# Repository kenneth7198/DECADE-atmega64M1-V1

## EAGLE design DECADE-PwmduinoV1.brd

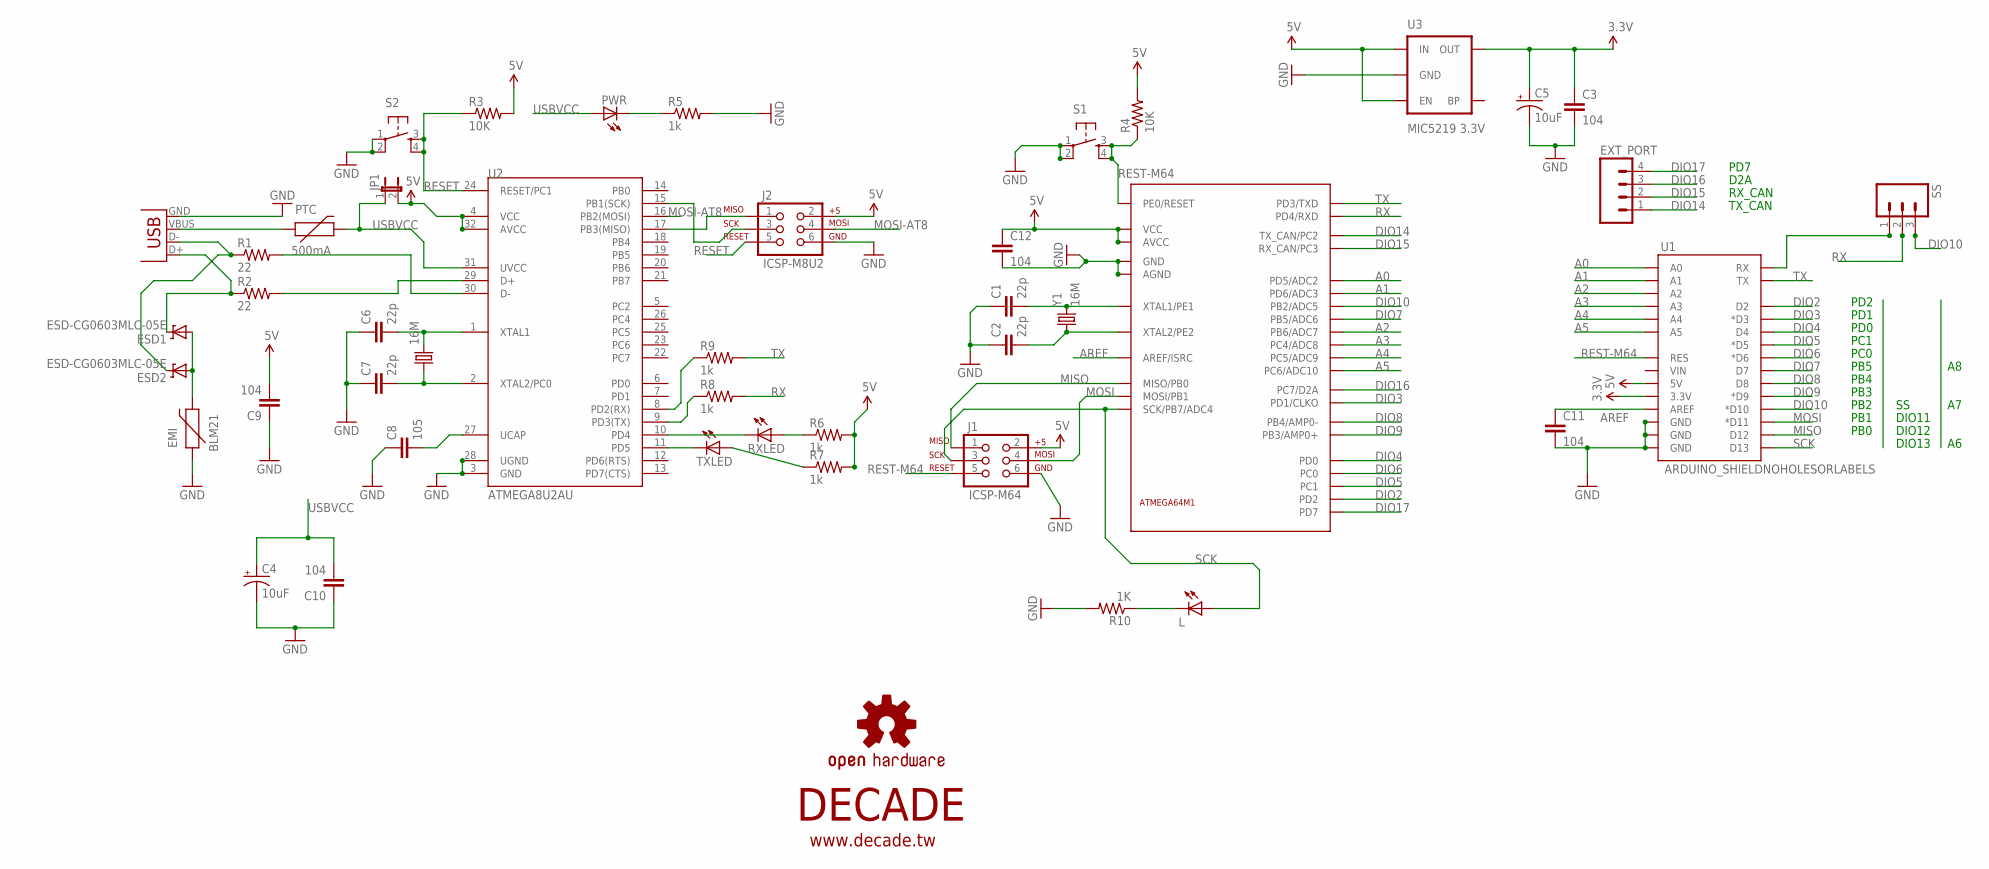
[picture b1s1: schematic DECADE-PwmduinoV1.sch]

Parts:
16M: CRYSTAL5X3; CRYSTAL-SMD-5X3
C1, C2, C6, C7: 22p; 0603-CAP
C3, C9, C10, C11, C12: 104; 0603-CAP
C4, C5: 10uF; EIA3216-KIT
C8: 105; 0603-CAP
EMI: BLM21; PTC-1206
ESD1, ESD2: ESD-CG0603MLC-05E; SOD-323
EXT_PORT: M04LOCK; 1X04_LOCK
J1: ICSP-M64; 2X3_LOCK
J2: ICSP-M8U2; 2X3_LOCK
JP1: JUMPER-2SMD-NO; SJ_2S-NO
L: LEDCHIP-LED0603; CHIP-LED0603
LOGO1: OSHW-LOGOL; OSHW-LOGO-L
PTC: 500mA; SPARKFUN_PTC-1206
PWR: LEDCHIP-LED0603; CHIP-LED0603
R1, R2: 22; SPARKFUN_0603-RES
R3, R4: 10K; SPARKFUN_0603-RES
R5, R6, R7, R8, R9: 1k; SPARKFUN_0603-RES
R10: 1K; SPARKFUN_0603-RES
RXLED: LEDCHIP-LED0603; CHIP-LED0603
S1: TAC_SWITCHPTH; TACTILE-PTH
S2: TAC_SWITCHSMD; TACTILE_SWITCH_SMD
SS: M03LOCK; 1X03_LOCK
TXLED: LEDCHIP-LED0603; CHIP-LED0603
U1: ARDUINO_SHIELDNOHOLESORLABELS; DUEMILANOVE_SHIELD_NOHOLES_NOLABELS
U2: ATMEGA8U2AU; TQFP32-08
U3: MIC5219 3.3V; SOT23-5
U$1: DECADE-ATMEGA64M1; DECADE-QFN-32
U$2: DECADE-LOGO-SMALL
X1: SPARKFUN_USBOLD; SPARKFUN_USB-MINIB-OLD
Y1: 16M; CRYSTAL-SMD-5X3

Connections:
3.3V: C3.1, C5.A (+), U1.3.3V, U3.5 (OUT)
5V: C9.2, C12.1, J1.2, J2.2, JP1.2, R3.2, R4.2, R6.2, R7.2, U1.5V, U2.4 (VCC), U2.32 (AVCC), U3.1 (IN), U3.3 (EN), U$1.4 (VCC), U$1.19 (AVCC)
A0: U1.A0, U$1.13 (PD5/ADC2)
A1: U1.A1, U$1.14 (PD6/ADC3)
A2: U1.A2, U$1.27 (PB6/ADC7)
A3: U1.A3, U$1.17 (PC4/ADC8)
A4: U1.A4, U$1.18 (PC5/ADC9)
A5: U1.A5, U$1.22 (PC6/ADC10)
AREF: C11.1, U1.AREF, U$1.21 (AREF/ISRC)
DIO2: U1.D2, U$1.1 (PD2)
DIO3: U1.D3 (*D3), U$1.32 (PD1/CLKO)
DIO4: U1.D4, U$1.29 (PD0)
DIO5: U1.D5 (*D5), U$1.3 (PC1)
DIO6: U1.D6 (*D6), U$1.30 (PC0)
DIO7: U1.D7, U$1.26 (PB5/ADC6)
DIO8: U1.D8, U$1.24 (PB4/AMP0-)
DIO9: U1.D9 (*D9), U$1.23 (PB3/AMP0+)
DIO10: SS.3, U1.D10 (*D10), U$1.16 (PB2/ADC5)
DIO14: EXT_PORT.1, U$1.6 (TX_CAN/PC2)
DIO15: EXT_PORT.2, U$1.7 (RX_CAN/PC3)
DIO16: EXT_PORT.3, U$1.25 (PC7/D2A)
DIO17: EXT_PORT.4, U$1.15 (PD7)
GND: C1.1, C2.1, C3.2, C4.C (-), C5.C (-), C6.1, C7.1, C8.1, C9.1, C10.1, C11.2, C12.2, EMI.1, J1.6, J2.6, R5.2, R10.2, S1.1, S1.2, S2.1, S2.2, U1.GND@0 (GND), U1.GND@1 (GND), U1.GND@2 (GND), U2.3 (GND), U2.28 (UGND), U3.2 (GND), U$1.5 (GND), U$1.20 (AGND), X1.GND
MISO: J1.1, U1.D12, U$1.8 (MISO/PB0)
MOSI: J1.4, U1.D11 (*D11), U$1.9 (MOSI/PB1)
MOSI-AT8: J2.4, U2.16 (PB2(MOSI))
unnamed: PTC.1, X1.VBUS
unnamed: 16M.3 (2), C6.2, U2.1 (XTAL1)
unnamed: 16M.1, C7.2, U2.2 (XTAL2/PC0)
unnamed: EMI.2, ESD1.2 (A), ESD2.2 (A)
unnamed: ESD2.1 (C), R1.1, X1.D-
unnamed: ESD1.1 (C), R2.1, X1.D+
unnamed: R1.2, U2.30 (D-)
unnamed: R2.2, U2.29 (D+)
unnamed: C2.2, U$1.11 (XTAL2/PE2), Y1.1
unnamed: C8.2, U2.27 (UCAP)
unnamed: C1.2, U$1.10 (XTAL1/PE1), Y1.3 (2)
unnamed: J2.1, U2.17 (PB3(MISO))
unnamed: J2.3, U2.15 (PB1(SCK))
unnamed: PWR.C, R5.1
unnamed: TXLED.C, U2.11 (PD5)
unnamed: RXLED.C, U2.10 (PD4)
unnamed: R6.1, RXLED.A
unnamed: R7.1, TXLED.A
unnamed: R9.1, U2.8 (PD2(RX))
unnamed: R8.1, U2.9 (PD3(TX))
unnamed: SS.1, U1.RX
unnamed: L.C, R10.1
RESET: J2.5, R3.1, S2.3, S2.4, U2.24 (RESET/PC1)
REST-M64: J1.5, R4.1, S1.3, S1.4, U1.RES, U$1.31 (PE0/RESET)
RX: R8.2, SS.2, U$1.12 (PD4/RXD)
SCK: J1.3, L.A, U1.D13, U$1.28 (SCK/PB7/ADC4)
TX: R9.2, U1.TX, U$1.2 (PD3/TXD)
USBVCC: C4.A (+), C10.2, JP1.1, PTC.2, PWR.A, U2.31 (UVCC)

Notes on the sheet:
PB0
PB1
PB2
PB3
PB4
PB5
PC0
PC1
PD0
PD1
PD2
TX_CAN
RX_CAN
D2A
PD7
DIO13
DIO12
DIO11

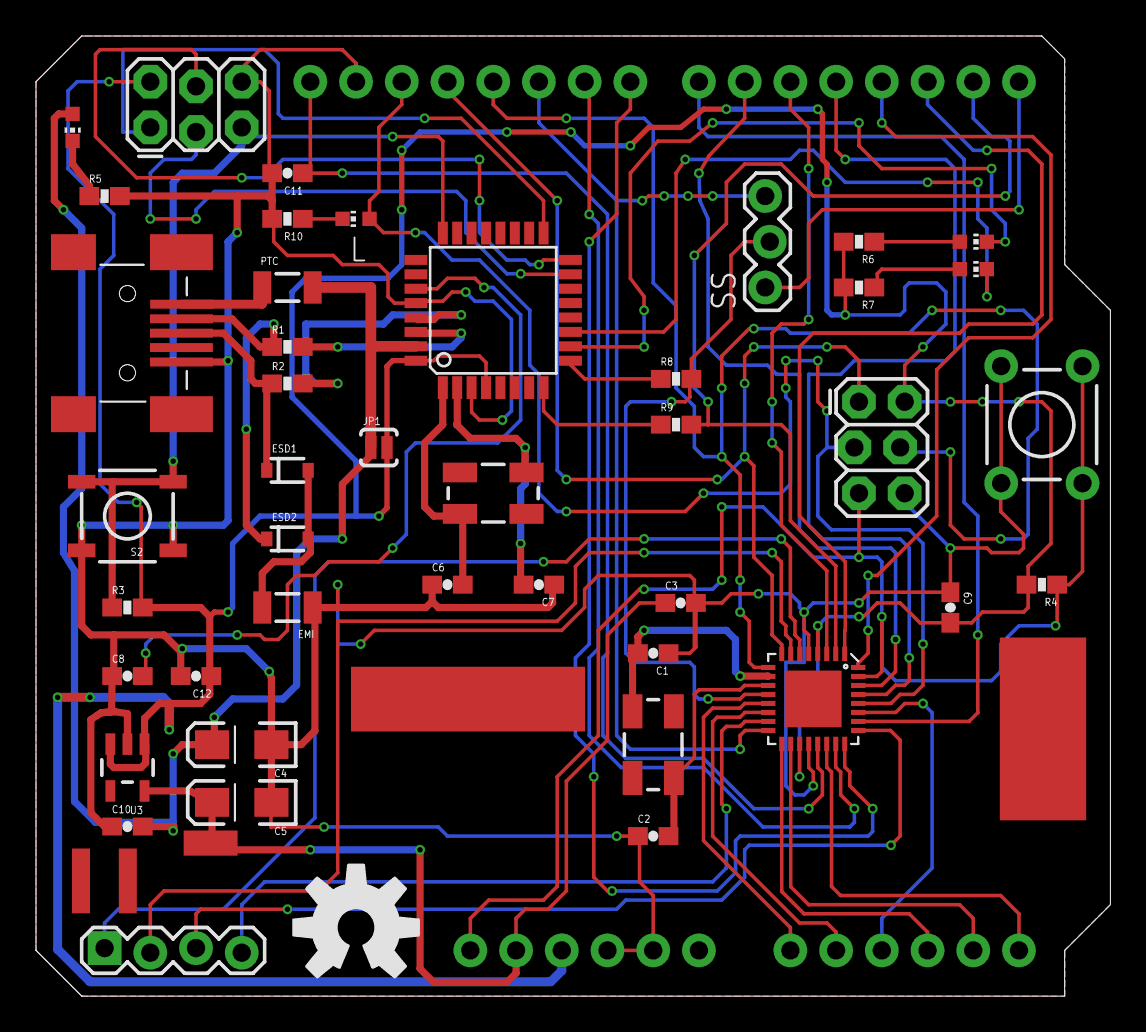
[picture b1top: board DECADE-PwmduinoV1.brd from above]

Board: 2 copper layers, 59.7 x 53.3 mm, 46 parts (0 on the bottom side), 54 nets.

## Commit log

2013-04-16 ATMEGA64M1
    first committed

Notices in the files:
parts and their libraries:
SparkFun-Boards: Licensing: CC v3.0 Share-Alike You are welcome to use this library for commercial purposes.
